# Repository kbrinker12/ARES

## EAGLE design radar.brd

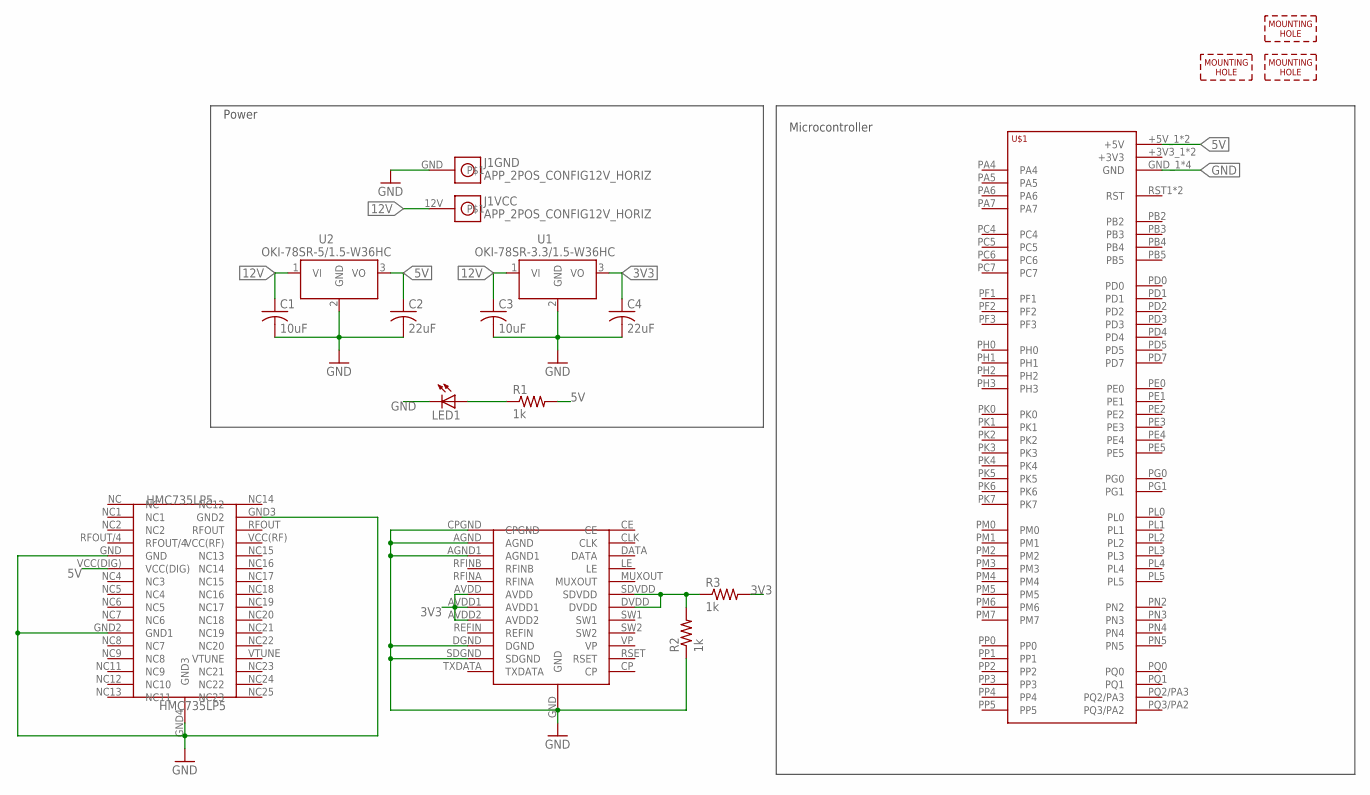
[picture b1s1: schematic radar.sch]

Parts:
C1, C3: 10uF; C0603
C2, C4: 22uF; C0603
H1, H2, H3: MOUNTING_HOLE#6; #6_SCREW
J1: APP_2POS_CONFIG12V_HORIZ; APP45_12V_HORIZ_CONFIG
LED1: LEDCHIP-LED0805; CHIP-LED0805
R1, R2, R3: 1k; M0805
U1: OKI-78SR-3.3/1.5-W36HC; OKI-78SR_HORIZ
U2: OKI-78SR-5/1.5-W36HC; OKI-78SR_HORIZ
U$1: TIVA-1294; TIVA-C-CONNECTED
U$2: HMC735LP5
U$3: ADF4169

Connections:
3V3: C4.1, R3.2, U1.3 (VO), U$3.AVDD, U$3.AVDD1, U$3.AVDD2
5V: C2.1, R1.2, U2.3 (VO), U$1.+5V_1 (+5V), U$1.+5V_2 (+5V), U$2.VCC(DIG)
12V: C1.1, C3.1, J1.12V, U1.1 (VI), U2.1 (VI)
GND: C1.2, C2.2, C3.2, C4.2, J1.GND, LED1.C, R2.1, U1.2 (GND), U2.2 (GND), U$1.GND_1 (GND), U$1.GND_2 (GND), U$1.GND_3 (GND), U$1.GND_4 (GND), U$2.GND, U$2.GND2 (GND1), U$2.GND3 (GND2), U$2.GND4 (GND3), U$3.AGND, U$3.AGND1, U$3.CPGND, U$3.DGND, U$3.GND, U$3.SDGND
unnamed: LED1.A, R1.1
unnamed: R2.2, R3.1, U$3.DVDD, U$3.SDVDD

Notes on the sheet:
Power
Microcontroller

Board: 2 copper layers, 17 parts (0 on the bottom side), 6 nets, no tracks yet.

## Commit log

2017-10-05 Start of PCB for Radar
2017-10-06 Finished VCO Package and placed it in schematic
2017-10-06 Created PLL library and added it to schematic
2017-10-06 Started board layout
2018-05-05 Final layout and schematic for project
